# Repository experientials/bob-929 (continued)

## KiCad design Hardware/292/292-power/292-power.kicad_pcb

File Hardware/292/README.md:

# 292 T-USB Module

You will revise my PCB design done with KiCAD v6. I have a schematic and basic PCB layout with the outline. 
The board takes data and power from two USB Type C connectors and routes it to two 50 pin connectors. 
In addition it has a 45 pin connector to enable extending the board with an Alt Mode signal. 

I will send you a link to the GitHub branch with the existing design. You must fork this and deliver a
Pull Request with the corrections.

You will review and fix:

- Schematic
- Component choice
- Resistor, Capacitor, Inductor, Diode sizes
- High speed signals
- PCB tolerances appropriate for JLCPCB/PCBWay manufacturing
- Footprints vs Datasheets
- good ESD/noise reduction circuits
- Update/Resolve Design checklist
- Ensure that differential pairs are routed together and balanced correctly
- Mounting half hole between the two three pin connectors
- 3D shapes

Route the board Symbols and footprints are found in https://github.com/experientials/kicad-lib.
I will need your GitHub username to give you read access.
For any changes to symbols, footprints and 3D shapes please create a GitHub Pull Request against the library.

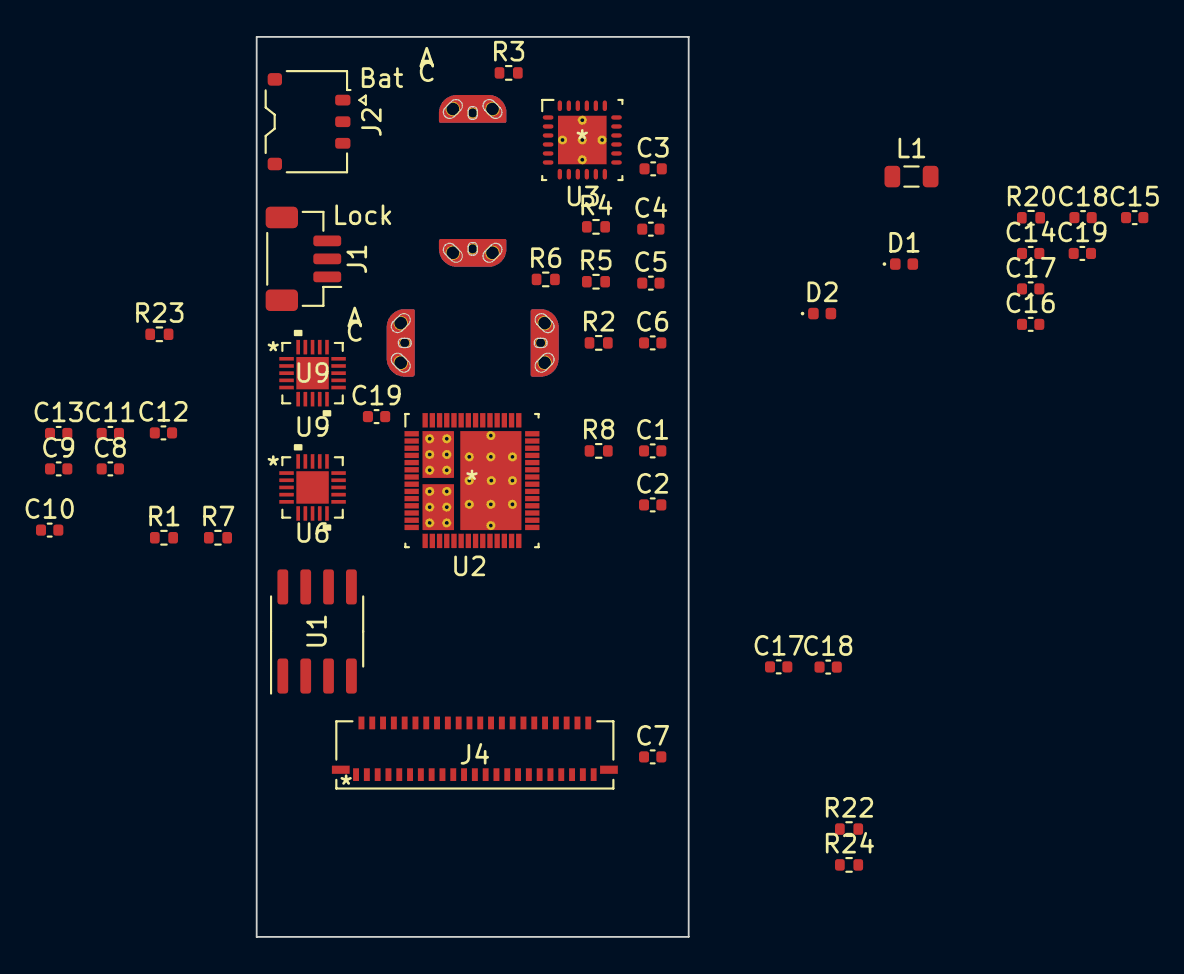
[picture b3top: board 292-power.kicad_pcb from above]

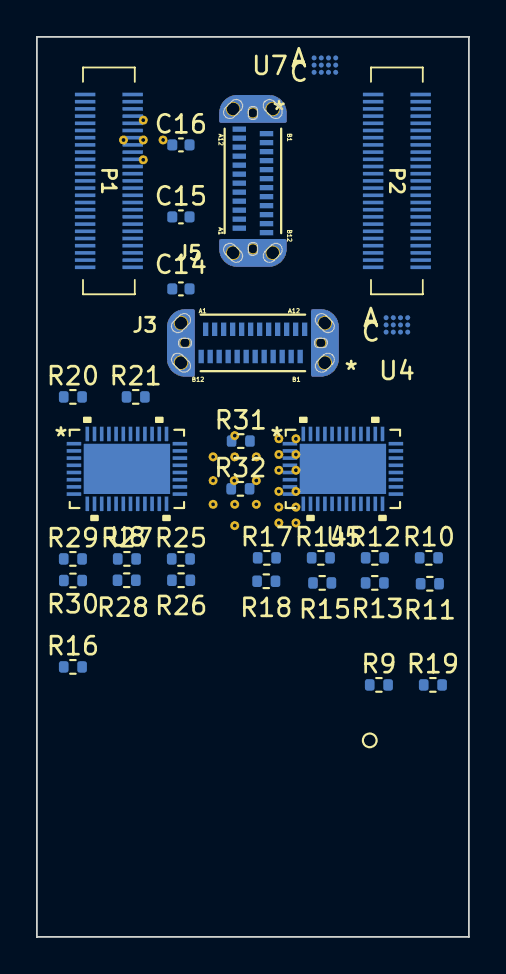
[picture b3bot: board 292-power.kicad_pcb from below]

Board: 2 copper layers, 24.0 x 50.0 mm, 77 parts (32 on the bottom side), 129 nets, no tracks yet.

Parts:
C1, C2, C3, C5: 22uF; C_0402_1005Metric
C4: 33nF; C_0402_1005Metric
C6: C; C_0402_1005Metric
C7, C12, C18#2: 1uF; C_0402_1005Metric
C8, C9, C10, C11, C14, C14#2, C15, C15#2, C16, C16#2, C17, C17#2, C18, C19: 100nF; C_0402_1005Metric
C13, C19#2: 0.1uF; C_0402_1005Metric
D1, D2: D_Schottky; D_0402_1005Metric
J1: Lock; JST_SH_BM03B-SRSS-TB_1x03-1MP_P1.00mm_Vertical
J2: Battery; JST_ACH_BM03B-ACHSS-GAN-ETF_1x03-1MP_P1.20mm_Vertical
J3: Host; HIROSE_CX80B1-24P
J4: ALT-HOST; 4-2328724-5
J5: OTG; HIROSE_CX80B1-24P
L1: L; L_0805_2012Metric
P1: HS; HRS_DF40C-50DS-0.4V(51)
P2: PW; HRS_DF40C-50DS-0.4V(51)
R1, R3, R4, R5, R6: R; R_0402_1005Metric
R2: 47K; R_0402_1005Metric
R7, R8, R10, R11, R12, R13, R14, R15, R17, R18, R19, R20, R20#2, R21, R24, R25, R26, R27, R28, R29, R30, R31, R32: 10K; R_0402_1005Metric
R9, R22: 150K; R_0402_1005Metric
R16, R23: 100K; R_0402_1005Metric
U1: W25X40CLSN; SOIC-8_3.9x4.9mm_P1.27mm
U2: RSH0056E; TPS65988DHRSHR
U3: RGE0024H; BQ24250RGER
U4, U7: TS5USBC410YFFR
U5, U8: RNQ40_TEX; TUSB546-DCIRNQT
U6: WQFN20_RUK_TEX; TPD6S300ARUKR
U9: U9; TPD6S300ARUKR

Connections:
/BAT_3V3: P2.40 (3V3), P2.43 (3V3)
/BAT_CE: P2.24 (BAT_CE#), U2.49 (GPIO17_PP_EXT2)
/BAT_EN: P2.25 (BAT_EN), U2.40 (GPIO12)
/BAT_INT: P2.23 (BAT_INT), U2.48 (GPIO16_PP_EXT1)
/FLASH_HOLD: P2.34 (FLASH_HOLD), U1.7 (~HOLD)
/HOST_D+: P2.6 (USB2_DP), U2.54 (C2_USB_P_GPIO20)
/HOST_D-: P2.7 (USB2_DN), U2.55 (C2_USB_N_GPIO21)
/Host USB-C Connector/DPEQ1: R10.2, R11.1, U5.2 (DPEQ1)
/Host USB-C Connector/EQ0: R14.2, R15.1, U5.38 (EQ0)
/Host USB-C Connector/EQ1: R17.2, R18.1, U5.35 (EQ1)
/Host USB-C Connector/HOST_D+: J3.A6 (D+), U4.C3 (D1+), U6.19 (D2)
/Host USB-C Connector/HOST_D-: J3.A7 (D-), U4.C4 (D1-), U6.20 (D1)
/Host USB-C Connector/OTG_XD+: J4.20 (HX+), U4.C1 (D2+)
/Host USB-C Connector/OTG_XD-: J4.21 (HX-), U4.C2 (D2-)
/Host USB-C Connector/POWER_SCL: J4.40 (POWER_SCL), U5.21 (FLIP/SCL)
/Host USB-C Connector/POWER_SDA: J4.41 (POWER_SDA), U5.22 (CTL0/SDA)
/Host USB-C Connector/RX1+: J3.B11 (RX1+), U5.30 (RX1P)
/Host USB-C Connector/RX1-: J3.B10 (RX1-), U5.31 (RX1N)
/Host USB-C Connector/RX2+: J3.A11 (RX2+), U5.40 (RX2P)
/Host USB-C Connector/RX2-: J3.A10 (RX2-), U5.39 (RX2N)
/Host USB-C Connector/SBU1: U5.27 (SBU1), U6.15 (SBU1)
/Host USB-C Connector/SBU2: U5.26 (SBU2), U6.14 (SBU2)
/Host USB-C Connector/SSEQ1: R12.2, R13.1, U5.3 (SSEQ1)
/Host USB-C Connector/TX1+: C10.2, U5.33 (TX1P)
/Host USB-C Connector/TX1-: C8.2, U5.34 (TX1N)
/Host USB-C Connector/TX2+: C9.2, U5.37 (TX2P)
/Host USB-C Connector/TX2-: C11.2, U5.36 (TX2N)
/Host USB-C Connector/USB_DX_SEL: U4.A1 (SEL1), U4.B2 (SEL2)
/Host USB-C Connector/VBUS: J3.A4 (VBUS), J3.A9 (VBUS), J3.B4 (VBUS), J3.B9 (VBUS)
/Host USB-C Connector/VIN_3V3: C12.1, C13.1, J4.1 (3V3), J4.4 (3V3), J4.7 (3V3), J4.10 (3V3), J4.13 (3V3), R7.1, R10.1, R12.1, R14.1, R16.1, R17.1, U4.B1 (VCC), U5.1 (VCC), U5.6 (VCC), U5.20 (VCC), U5.28 (VCC), U6.10 (VPWER)
/LDO_3V3: R1.1, U1.8 (VCC)
/LOCK_BTN: P2.28 (LOCK_BTN), U2.41 (GPIO13)
/OTG USB-C Connector/DPEQ1: R25.2, R26.1, U8.2 (DPEQ1)
/OTG USB-C Connector/EQ0: R29.2, R30.1, U8.38 (EQ0)
/OTG USB-C Connector/EQ1: R31.2, R32.1, U8.35 (EQ1)
/OTG USB-C Connector/OTG_D+: J5.A6 (D+), U7.C3 (D1+), U9.19 (D2)
/OTG USB-C Connector/OTG_D-: J5.A7 (D-), U7.C4 (D1-), U9.20 (D1)
/OTG USB-C Connector/RX1+: J5.B11 (RX1+), U8.30 (RX1P)
/OTG USB-C Connector/RX1-: J5.B10 (RX1-), U8.31 (RX1N)
/OTG USB-C Connector/RX2+: J5.A11 (RX2+), U8.40 (RX2P)
/OTG USB-C Connector/RX2-: J5.A10 (RX2-), U8.39 (RX2N)
/OTG USB-C Connector/SSEQ1: R27.2, R28.1, U8.3 (SSEQ1)
/OTG USB-C Connector/TX1+: C16#2.2, U8.33 (TX1P)
/OTG USB-C Connector/TX1-: C14#2.2, U8.34 (TX1N)
/OTG USB-C Connector/TX2+: C15#2.2, U8.37 (TX2P)
/OTG USB-C Connector/TX2-: C17#2.2, U8.36 (TX2N)
/OTG USB-C Connector/USB_DX_SEL: U7.A1 (SEL1), U7.B2 (SEL2)
/OTG USB-C Connector/VBUS: J5.A4 (VBUS), J5.A9 (VBUS), J5.B4 (VBUS), J5.B9 (VBUS)
/OTG USB-C Connector/VIN_3V3: C18#2.1, C19.1, C19#2.1, R20#2.1, R23.1, R25.1, R27.1, R29.1, R31.1, U7.B1 (VCC), U8.1 (VCC), U8.6 (VCC), U8.20 (VCC), U8.28 (VCC), U9.10 (VPWER)
/OTG USB-C Connector/VIN_5V: C18.1, R20.2
/OTG_D+: P2.3 (USB1_DP), U2.50 (C1_USB_P_GPIO18)
/OTG_D-: P2.4 (USB1_DN), U2.53 (C1_USB_N_GPIO19)
/PD_HRESET: P2.39 (PD_HRESET), U2.44 (HRESET)
/POWER SCL: P2.36 (POWER_SCL), U2.21 (I2C3_SCL_GPIO5)
/POWER SDA: P2.35 (POWER_SDA), U2.22 (I2C3_SDA_GPIO6)
/POWER_PD_CTL_INT: P2.37 (POWER_PD_CTL_INT), U2.23 (I2C3_IRQ_GPIO7_N)
/Power Part/BAT_CE_N: R2.1, U3.1 (CE_N)
/Power Part/BAT_EN: U3.2 (EN1), U3.3 (EN2)
/Power Part/BAT_LDO: C3.1, R6.2, U3.24 (LDO)
/Power Part/HOST_VBUS: D1.1 (K), U2.3 (VBUS2), U2.4 (VBUS2)
/Power Part/OTG_VBUS: D2.1 (K), U2.13 (VBUS1), U2.14 (VBUS1)
/Power Part/PD_LDO_3V3: J1.2, U2.9 (LDO_3V3)
/Power Part/PWR_CHARGE: C1.1, U2.1 (PP_HV2), U2.2 (PP_HV2), U2.11 (PP_HV1), U2.12 (PP_HV1), U3.19 (IN)
/Power Part/VSOM: C5.1, C6.1, L1.2, U3.13 (SYS), U3.14 (SYS)
/SPI_CLK: P2.32 (SPI_CLK), U1.6 (SCK), U2.38 (SPI_CLK_GPIO10)
/SPI_MISO: P2.31 (SPI_MISO), U1.2 (DO(IO1)), U2.36 (SPI_MISO_GPIO8)
/SPI_MOSI: P2.30 (SPI_MOSI), U1.5 (DI(IO0)), U2.37 (SPI_MOSI_GPIO9)
/SPI_SS: P2.33 (SPI_CS), U1.1 (~CS), U2.39 (SPI_SS_GPIO11_N)
/STEM SCL: P1.17 (STEM_SCL), U2.27 (I2C1_SCL)
/STEM SDA: P1.18 (STEM_SDA), U2.28 (I2C1_SDA)
/SYS SCL: P2.13 (SYS_I2C_SCL), U2.32 (I2C2_SCL)
/SYS SDA: P2.14 (SYS_I2C_SDA), U2.33 (I2C2_SDA)
/SYS_PD_CTL_INT: P2.12 (SYS_PD_CTL_INT), U2.34 (I2C2_IRQ_N)
/USB_XD_OE: P2.16 (USB_XD_OE), U2.17 (GPIO1)
/USB_XD_SEL: P2.17 (USB_XD_SEL), U2.18 (GPIO2)
/VSOM: P1.1 (VSOM), P1.26 (VSOM), P1.36 (VSOM), P1.39 (VSOM), P1.42 (VSOM), P1.45 (VSOM), P1.48 (VSOM), P2.1 (VSOM), P2.15 (VSOM), P2.26 (VSOM)
GND: C1.2, C2.2, C3.2, C5.2, C6.2, C7.2, C12.2, C18.2, C18#2.2, C19.2, D1.2 (A), D2.2 (A), J2.3, J3.A1 (GND), J3.A12 (GND), J3.B1 (GND), J3.B12 (GND), J3.S1 (SHIELD), J4.16 (GND), J4.19 (GND), J4.24 (GND), J4.27 (GND), J4.30 (GND), J4.33 (GND), J4.36 (GND), J4.39 (GND), J5.A1 (GND), J5.A12 (GND), J5.B1 (GND), J5.B12 (GND), J5.S1 (SHIELD), P1.4 (GND), P1.7 (GND), P1.10 (GND), P1.13 (GND), P1.20 (GND), P1.33 (GND), P2.2 (GND), P2.5 (GND), P2.8 (GND), P2.11 (GND), R2.2, R3.2, R4.2, R5.2, R8.2, R9.2, R11.2, R13.2, R15.2, R18.2, R21.2, R22.2, R26.2, R28.2, R30.2, R32.2, U1.4 (GND), U2.7 (DRAIN2), U2.8 (DRAIN1), U2.15 (DRAIN1), U2.19 (DRAIN1), U2.20 (GND), U2.51 (GND), U2.52 (DRAIN2), U2.56 (DRAIN2), U2.57 (DRAIN2), U2.58 (DRAIN1), U2.59 (GND), U3.4 (AGND), U3.15 (PGND), U3.16 (PGND), U3.25 (PAD), U4.B3 (GND), U5.41 (EPAD), U6.8 (GND), U6.13 (GND), U6.18 (GND), U6.21 (GND), U7.B3 (GND), U8.41 (EPAD), U9.8 (GND), U9.13 (GND), U9.18 (GND), U9.21 (GND)
unnamed: C2.1, U2.25 (PP1_CABLE), U2.46 (PP2_CABLE)
unnamed: C4.1, L1.1, U3.17 (SW), U3.18 (SW)
unnamed: C4.2, U3.21 (BOOT)
unnamed: C7.1, J2.1, U3.11 (BAT), U3.12 (BAT)
unnamed: C8.1, J3.A3 (TX1-)
unnamed: C9.1, J3.B2 (TX2+)
unnamed: C10.1, J3.A2 (TX1+)
unnamed: C11.1, J3.B3 (TX2-)
unnamed: C13.2, U6.3 (VBIAS)
unnamed: C19#2.2, U9.3 (VBIAS)
unnamed: J2.2, R5.1, R6.1, U3.9 (TS)
unnamed: J3.A5 (CC1), U6.4 (C_CC1), U6.7 (RPD_G1)
unnamed: J3.A8 (SBU1), U6.1 (C_SBU1)
unnamed: J3.B5 (CC2), U6.5 (C_CC2), U6.6 (RPD_G2)
unnamed: J3.B6 (D+), U4.A2 (D+)
unnamed: J3.B7 (D-), U4.A3 (D-)
unnamed: J3.B8 (SBU2), U6.2 (C_SBU2)
unnamed: J4.2 (AUXN), U5.25 (AUXN)
unnamed: J4.3 (AUXP), U5.24 (AUXP)
unnamed: J4.5 (HA+), U5.9 (DP0P)
unnamed: J4.6 (HA-), U5.10 (DP0N)
unnamed: J4.8 (HB+), U5.12 (DP1P)
unnamed: J4.9 (HB-), U5.13 (DP1N)
unnamed: J4.11 (HC+), U5.15 (DP2P)
unnamed: J4.12 (HC-), U5.16 (DP2N)
unnamed: J4.14 (HD+), U5.18 (DP3P)
unnamed: J4.15 (HD-), U5.19 (DP3N)
unnamed: J4.22 (HPDIN), U5.23 (CTL1/HPDIN)
unnamed: C16#2.1, J5.A2 (TX1+)
unnamed: C14#2.1, J5.A3 (TX1-)
unnamed: J5.A5 (CC1), U9.4 (C_CC1), U9.7 (RPD_G1)
unnamed: J5.A8 (SBU1), U9.1 (C_SBU1)
unnamed: C15#2.1, J5.B2 (TX2+)
unnamed: C17#2.1, J5.B3 (TX2-)
unnamed: J5.B5 (CC2), U9.5 (C_CC2), U9.6 (RPD_G2)
unnamed: J5.B6 (D+), U7.A3 (D-)
unnamed: J5.B7 (D-), U7.A2 (D+)
unnamed: J5.B8 (SBU2), U9.2 (C_SBU2)
unnamed: P1.19 (STEM_INT), U2.29 (I2C1_IRQ_N)
unnamed: R1.2, U1.3 (~WP)
unnamed: R3.1, U3.22 (ILIM)
unnamed: R4.1, U3.10 (ISET)
unnamed: R7.2, U5.11 (SSEQ0/A0)
unnamed: R8.1, U5.14 (DPEQ0/A1)
unnamed: R9.1, U5.29 (CAD_SNK/)
unnamed: R16.2, U6.9 (FLT)
unnamed: R19.2, U5.17 (I2C_EN)
unnamed: R20#2.2, U8.11 (SSEQ0/A0)
unnamed: R21.1, U8.14 (DPEQ0/A1)
unnamed: R22.1, U8.29 (CAD_SNK/)
unnamed: R23.2, U9.9 (FLT)
unnamed: R24.2, U8.17 (I2C_EN)

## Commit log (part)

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2022-08-31 Basic Plan
2022-08-31 Combined Camera module 202
2022-09-02 Added MSP430
    This will be the only expander in the future. Experiment for now
2022-09-16 Schematic clean-up
    -Cleaned-up shcematics
    -Added a TVS diode array to the SDCard connector.
    -Impedances are calculated
2022-09-18 292 Power Module document
2022-09-18 292 KiCAD and datasheets
2022-09-18 Add files via upload
    Mostly Routed
2022-09-20 Add files via upload
    ROuting completed, differential pairs are length matched and tuned
2022-09-23 Draft board design
2022-09-25 Clarifications for the board plan
2022-09-26 Add files via upload
    - PCB is converted to 6-layer board
    - Differential pairs are routed and matched
    - Footprint of the LDO is changed to DFN (TPS79628DRBT is in use now)
    - Small changes which were causing DRC errors where corrected in Ziloo footprint library.
2022-10-04 Moved power/lock connectors
    Need space to place batteries
2022-10-07 Don’t commit backups
2022-11-13 First review based revision
2022-11-13 Added battery details
2022-11-13 Faceboard design
2022-11-13 Removed VSOM diodes
2022-11-13 Added components
    ESD HDMI
    Extra components planned
2022-11-13 M7 workload
2022-11-27 PoC board task
2022-11-28 Remove KiCad backups
2022-12-05 PCB screw holes and rounded corners
